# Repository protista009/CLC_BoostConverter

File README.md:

# CLC Boost Converter

A closed-loop, PID-controlled boost converter for DC-DC voltage regulation, featuring MATLAB simulation models and adaptable microcontroller firmware. This project demonstrates real-time analog feedback and PWM control for stable power supply.

---

## Features

- Closed-loop PID control for accurate voltage regulation
- MATLAB/Simulink models for system simulation
- Example firmware for analog and PWM-capable microcontrollers

---

## Hardware and Pinout

- Output voltage sensed via resistor divider to analog input
- PWM output pin drives MOSFET gate in boost converter stage
- Compatible with various microcontrollers

---

## Setup and Usage

1. Connect voltage divider to microcontroller analog input
2. Connect PWM-capable output pin to MOSFET gate driver
3. Power the system safely
4. Upload and run the firmware
5. Monitor real-time feedback for verification

---

## Requirements

- MATLAB/Simulink (for simulation)
- Microcontroller with analog input and PWM output (e.g., Arduino, STM32, ESP32)
- Circuit prototyping tools

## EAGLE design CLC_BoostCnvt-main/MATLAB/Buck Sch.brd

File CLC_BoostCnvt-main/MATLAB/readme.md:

# CLC Boost Converter

A closed-loop, PID-controlled boost converter for DC-DC voltage regulation, featuring MATLAB simulation models and adaptable microcontroller firmware. This project demonstrates real-time analog feedback and PWM control for stable power supply.

---

## Features

- Closed-loop PID control for accurate voltage regulation
- MATLAB/Simulink models for system simulation
- Example firmware for analog and PWM-capable microcontrollers

---

## Hardware and Pinout

- Output voltage sensed via resistor divider to analog input
- PWM output pin drives MOSFET gate in boost converter stage
- Compatible with various microcontrollers

---

## Setup and Usage

1. Connect voltage divider to microcontroller analog input
2. Connect PWM-capable output pin to MOSFET gate driver
3. Power the system safely
4. Upload and run the firmware
5. Monitor real-time feedback for verification

---

## Requirements

- MATLAB/Simulink (for simulation)
- Microcontroller with analog input and PWM output (e.g., Arduino, STM32, ESP32)
- Circuit prototyping tools

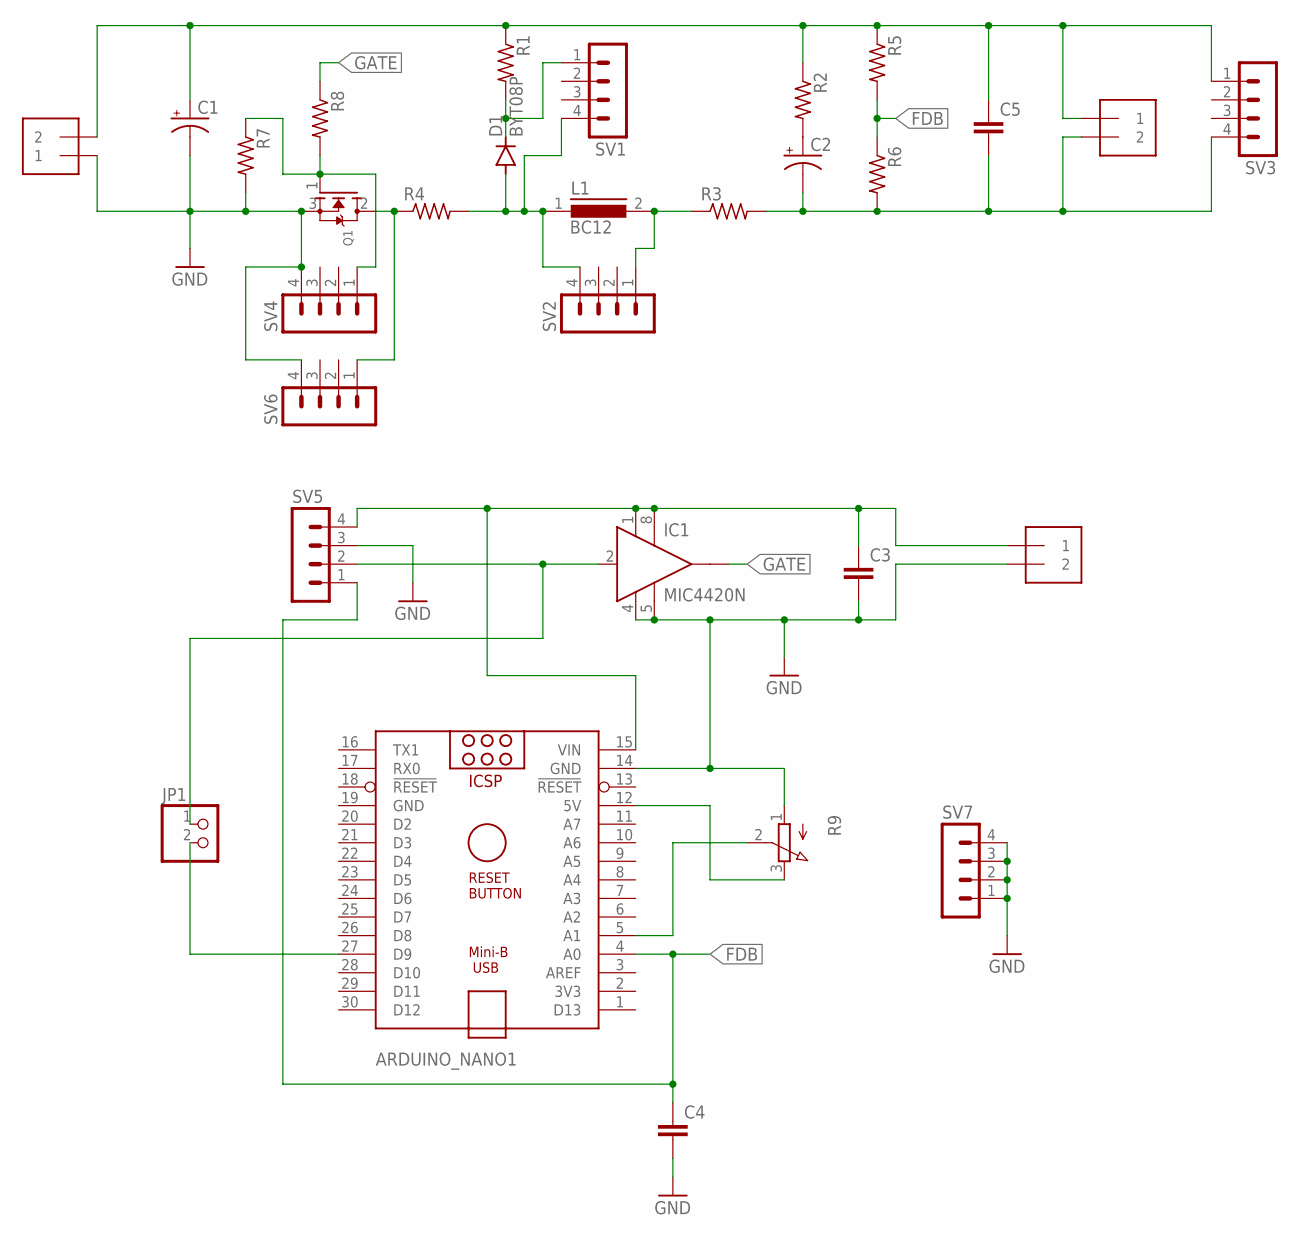
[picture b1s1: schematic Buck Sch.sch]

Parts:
ARDUINO_NANO1: ARDUINO_NANO
C1, C2: CPOL-USE5-10.5; E5-10,5
C3, C4: C2,5-3; C2.5-3
C5: C-EU050-024X044; C050-024X044
D1: BYT08P; TO220ACS
IC1: MIC4420N; DIL08
J1, J2, J3: 1X2-3.5MM
JP1: PINHD-1X2; 1X02
L1: BC12
Q1: MOSFET-NGDS_TO220V; TO220V
R1, R2, R3, R4: R-US_0414/15; 0414/15
R5, R6, R7: R-US_0204/7; 0204/7
R8: R-US_0309/12; 0309/12
R9: 3RP/1610N
SV1, SV2, SV3, SV4, SV5, SV6, SV7: MA04-1

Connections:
FDB: ARDUINO_NANO1.4 (A0), C4.1, R5.2, R6.1, SV5.1
GATE: IC1.6 (OUT), R8.1
GND: ARDUINO_NANO1.14 (GND), ARDUINO_NANO1.19 (GND), C1.-, C3.2, C4.2, IC1.4 (GND), IC1.5 (GND1), J1.2, J3.1, Q1.3 (S), R7.2, R9.1 (A), SV4.4, SV5.3, SV6.4, SV7.1, SV7.2, SV7.3, SV7.4
unnamed: C1.+, C5.1, J2.1, J3.2, R1.1, R2.1, R5.1, SV3.1
unnamed: ARDUINO_NANO1.5 (A1), R9.2 (S)
unnamed: C2.-, C5.2, J2.2, R3.2, R6.2, SV3.4
unnamed: D1.A, L1.1, R4.2, SV1.4, SV2.4
unnamed: D1.C, R1.2, SV1.1
unnamed: C2.+, R2.2
unnamed: L1.2, R3.1, SV2.1
unnamed: Q1.2 (D), R4.1, SV6.1
unnamed: ARDUINO_NANO1.15 (VIN), C3.1, IC1.1 (VS), IC1.8 (VS1), J1.1, SV5.4
unnamed: Q1.1 (G), R7.1, R8.2, SV4.1
unnamed: IC1.2 (IN), JP1.1, SV5.2
unnamed: ARDUINO_NANO1.12 (5V), R9.3 (E)
unnamed: ARDUINO_NANO1.27 (D9), JP1.2

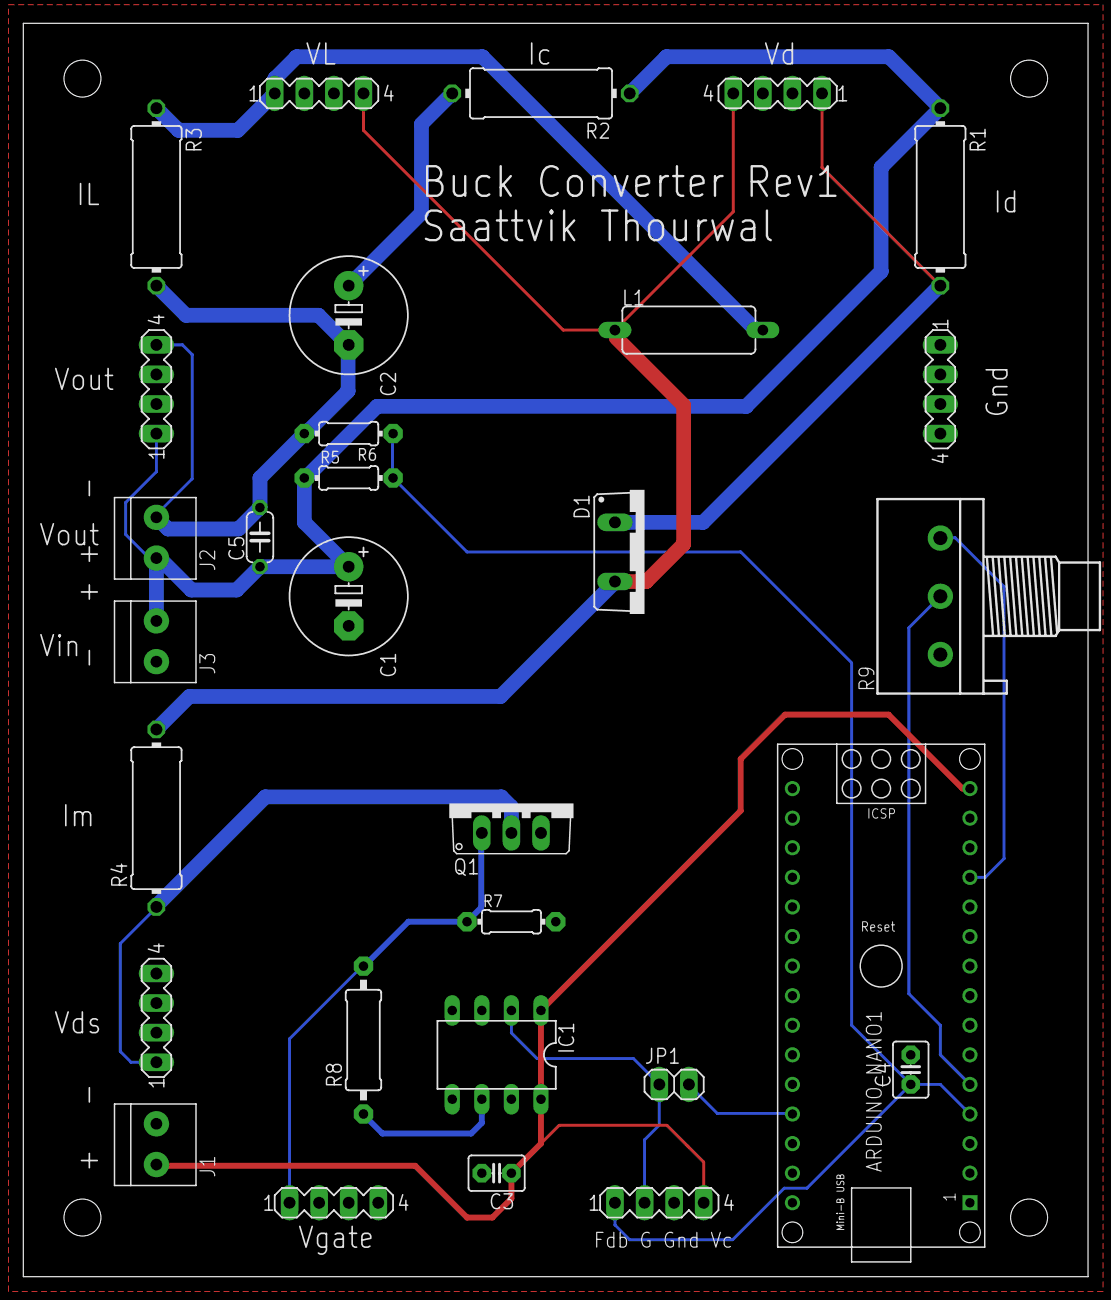
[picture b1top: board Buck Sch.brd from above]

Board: 2 copper layers, 91.4 x 107.6 mm, 30 parts (0 on the bottom side), 16 nets.

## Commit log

2025-10-17 Fix typo in readme.md
2025-10-17 updated readme
    Added detailed project description, features, hardware pinout, and setup instructions to the readme file.
2025-10-17 Revised
    Updated the readme to enhance clarity and detail about the boost converter project, including features, setup instructions, and requirements.
2025-10-17 readme
